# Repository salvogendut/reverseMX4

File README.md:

# reverseMX4: four-slot CPC edge backplane

This project is a four-slot expansion backplane for the Amstrad CPC bus. A short cable connects the computer to a **50-contact male edge tongue on the backplane**. Four vertical, 50-contact female card-edge sockets accept expansion cards that have the classic CPC edge finger pattern. There are no MX4/IDC headers on the backplane.

## Target computers

- CPC 464, 664 and 6128: cable with a 50-contact female edge socket at the computer.
- CPC 464 Plus and 6128 Plus: cable with a 50-contact Delta/Amphenol style plug at the computer.
- The board-end of either cable has a 50-contact female edge socket. The cable must map each **named signal** to the backplane tongue contact in [`docs/cpc-expansion-pinout.csv`](docs/cpc-expansion-pinout.csv); do not rely on the shell orientation or ribbon stripe alone.

The classic CPC expansion port has 25 contacts on each face, 2.54 mm pitch and 1.6 mm nominal card thickness. The Plus uses a 50-contact Delta style connector with the same bus signals. The board does not translate logic or select slots; all four sockets share the expansion bus in parallel. Expansion cards must themselves handle address decoding and bus arbitration. Simultaneous use also depends on the computer's available power and the attached cards' electrical loading.

## Prototype design

- [`reverseMX4.kicad_sch`](reverseMX4.kicad_sch), [`reverseMX4.kicad_pcb`](reverseMX4.kicad_pcb) and [`reverseMX4.kicad_pro`](reverseMX4.kicad_pro) are the editable KiCad 10 project.
- Board outline: 100 × 200 mm including the 65.74 mm wide cable tongue. Four EDAC 50-contact sockets are placed at 35 mm slot pitch.
- Four copper layers: odd-side bus signals on inner layer 1, even-side bus signals on inner layer 2, selected 5 V fill on front, ground fill on back.
- `JP1` selects CPC power (pins 1–2) or external regulated 5 V (pins 2–3). The external input passes through a 3 A hold PTC fuse. The sources are isolated from each other by the removed position of the shunt.
- The 50 tongue pads stop 0.6 mm before the board tip. The EDAC drawing places the contact point approximately 4.06 mm behind the tip, within the 6.9 mm long contact pad. The socket's recommended daughter-board width is 66.04 − 0.30 = 65.74 mm.
- [`docs/assembly.md`](docs/assembly.md) covers cable checks, part placement and manufacturing notes. [`docs/bom.csv`](docs/bom.csv) lists parts. [`docs/preview/schematic.pdf`](docs/preview/schematic.pdf) and [`docs/preview/top-assembly.svg`](docs/preview/top-assembly.svg) are review views.
- [`fab/reverseMX4-A0-gerbers.zip`](fab/reverseMX4-A0-gerbers.zip) contains the four copper layers, masks, silkscreens, outline and separate plated/non-plated drill files. Read [`fab/README.md`](fab/README.md) before ordering.

## 3D rendering

[Open the full-size 3D rendering](docs/preview/board-3d.png). The four socket bodies use a simple local preview model to show position and card openings; their exact housing shape and height have not been verified against a physical EDAC part.

KiCad ERC and DRC pass with zero violations, zero unrouted items and zero schematic parity issues. The PCB is an **untested prototype**: connector mating, card clearance, cable orientation and operation on real CPC/CPC Plus computers still need physical verification before a production run.

The reference URL supplied for this project, `rabs664/Amstrad-CPC-Plus-Expansion-Backplane`, was unavailable during the initial research. Its layout has not been copied. The pin map below comes from Amstrad's CPC 464 manual and Arnold V CPC Plus expansion specification.

## Sources

- [Amstrad CPC 464 user manual, expansion connector page](https://www.manualslib.com/manual/862146/Amstrad-Cpc464.html?page=237)
- [Amstrad Arnold V specification, appendix II](https://www.cpctech.cpcwiki.de/docs/arn5new.html)
- [EDAC 345/395 card-edge connector datasheet](https://www.farnell.com/datasheets/2916867.pdf)
- [CPC expansion power notes](https://www.cpctech.cpcwiki.de/docs/signals.html)
- [EDAC 395 series product specifications](https://edac.net/series/395)

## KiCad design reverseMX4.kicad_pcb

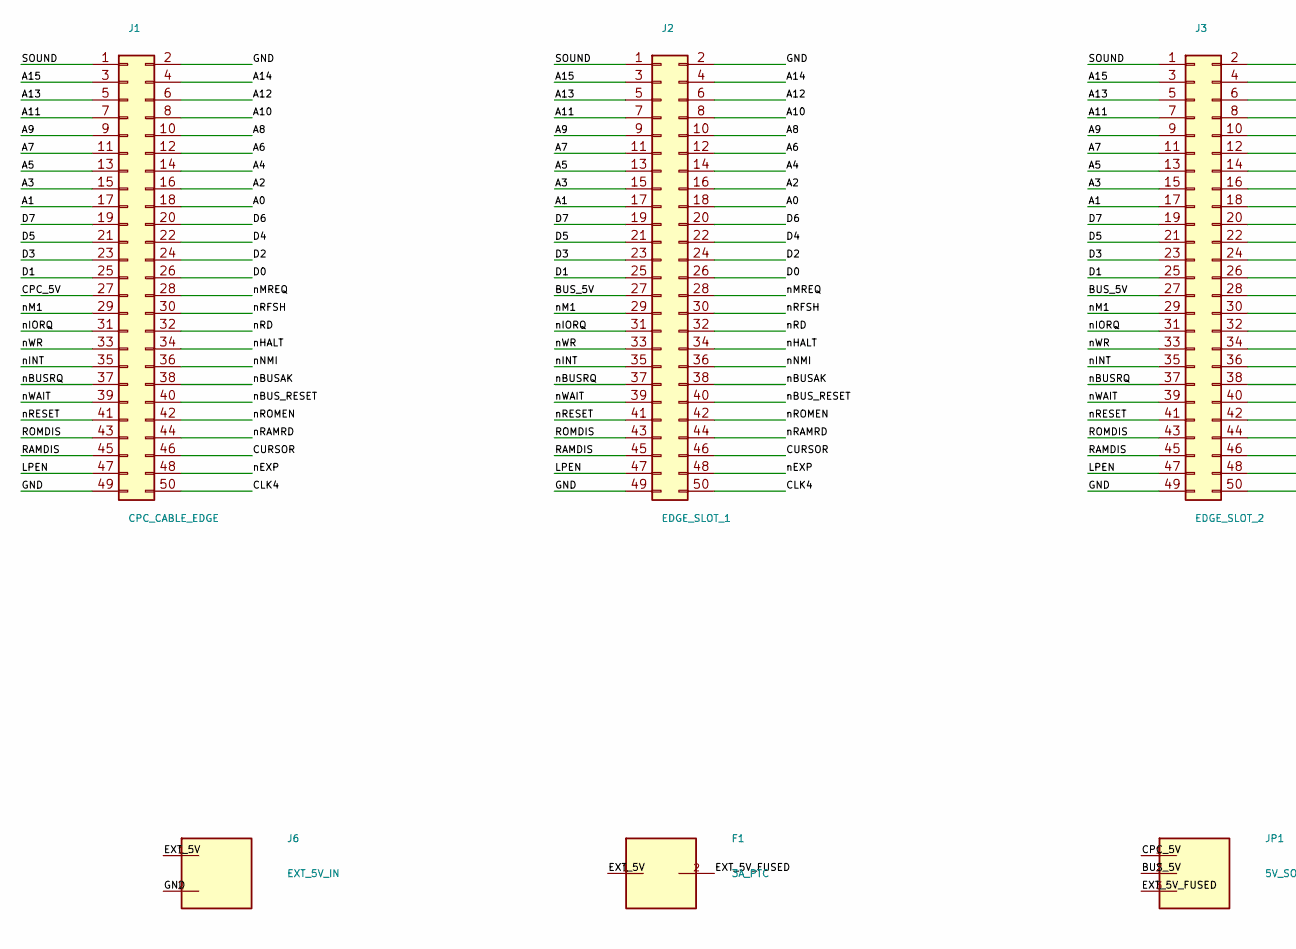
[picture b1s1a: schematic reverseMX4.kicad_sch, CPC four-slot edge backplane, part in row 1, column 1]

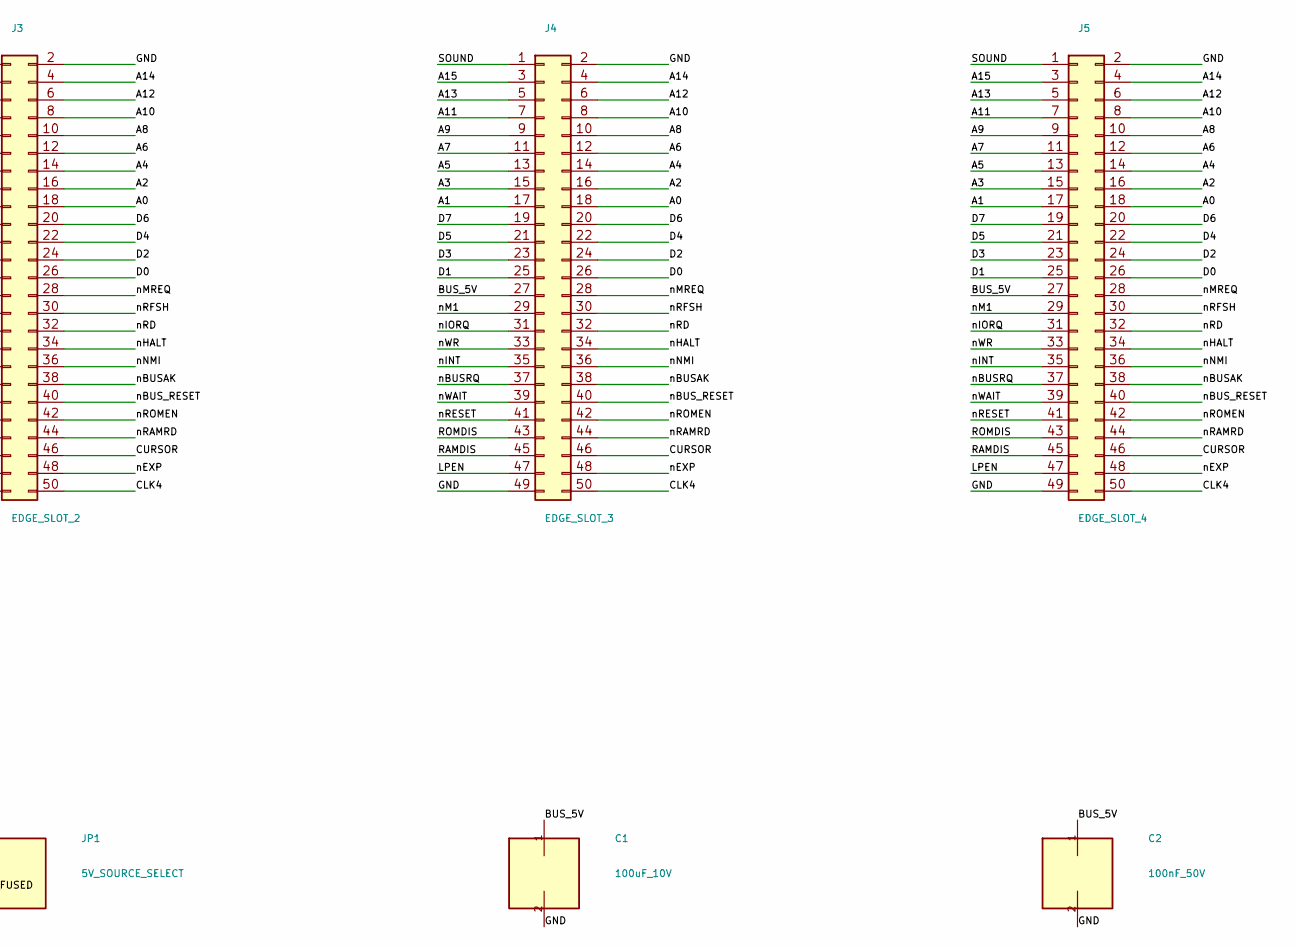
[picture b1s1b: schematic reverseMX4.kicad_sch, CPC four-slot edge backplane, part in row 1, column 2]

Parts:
C1: 100uF_10V; CP_Radial_D6.3mm_P2.50mm
C2: 100nF_50V; C_Disc_D3.0mm_W1.6mm_P2.50mm
F1: 3A_PTC; Fuse_Bourns_MF-RG300
J1: CPC_CABLE_EDGE; CPC_Edge_2x25
J2: EDGE_SLOT_1; EDAC_395-050-521-204
J3: EDGE_SLOT_2; EDAC_395-050-521-204
J4: EDGE_SLOT_3; EDAC_395-050-521-204
J5: EDGE_SLOT_4; EDAC_395-050-521-204
J6: EXT_5V_IN; TerminalBlock_Phoenix_MKDS-1,5-2_1x02_P5.00mm_Horizontal
JP1: 5V_SOURCE_SELECT; PinHeader_1x03_P2.54mm_Vertical

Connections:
/A0: J1.18, J2.18, J3.18, J4.18, J5.18
/A1: J1.17, J2.17, J3.17, J4.17, J5.17
/A2: J1.16, J2.16, J3.16, J4.16, J5.16
/A3: J1.15, J2.15, J3.15, J4.15, J5.15
/A4: J1.14, J2.14, J3.14, J4.14, J5.14
/A5: J1.13, J2.13, J3.13, J4.13, J5.13
/A6: J1.12, J2.12, J3.12, J4.12, J5.12
/A7: J1.11, J2.11, J3.11, J4.11, J5.11
/A8: J1.10, J2.10, J3.10, J4.10, J5.10
/A9: J1.9, J2.9, J3.9, J4.9, J5.9
/A10: J1.8, J2.8, J3.8, J4.8, J5.8
/A11: J1.7, J2.7, J3.7, J4.7, J5.7
/A12: J1.6, J2.6, J3.6, J4.6, J5.6
/A13: J1.5, J2.5, J3.5, J4.5, J5.5
/A14: J1.4, J2.4, J3.4, J4.4, J5.4
/A15: J1.3, J2.3, J3.3, J4.3, J5.3
/BUS_5V: C1.1, C2.1, J2.27, J3.27, J4.27, J5.27, JP1.2
/CLK4: J1.50, J2.50, J3.50, J4.50, J5.50
/CPC_5V: J1.27, JP1.1
/CURSOR: J1.46, J2.46, J3.46, J4.46, J5.46
/D0: J1.26, J2.26, J3.26, J4.26, J5.26
/D1: J1.25, J2.25, J3.25, J4.25, J5.25
/D2: J1.24, J2.24, J3.24, J4.24, J5.24
/D3: J1.23, J2.23, J3.23, J4.23, J5.23
/D4: J1.22, J2.22, J3.22, J4.22, J5.22
/D5: J1.21, J2.21, J3.21, J4.21, J5.21
/D6: J1.20, J2.20, J3.20, J4.20, J5.20
/D7: J1.19, J2.19, J3.19, J4.19, J5.19
/EXT_5V: F1.1, J6.1
/EXT_5V_FUSED: F1.2, JP1.3
/GND: C1.2, C2.2, J1.2, J1.49, J2.2, J2.49, J3.2, J3.49, J4.2, J4.49, J5.2, J5.49, J6.2
/LPEN: J1.47, J2.47, J3.47, J4.47, J5.47
/RAMDIS: J1.45, J2.45, J3.45, J4.45, J5.45
/ROMDIS: J1.43, J2.43, J3.43, J4.43, J5.43
/SOUND: J1.1, J2.1, J3.1, J4.1, J5.1
/nBUSAK: J1.38, J2.38, J3.38, J4.38, J5.38
/nBUSRQ: J1.37, J2.37, J3.37, J4.37, J5.37
/nBUS_RESET: J1.40, J2.40, J3.40, J4.40, J5.40
/nEXP: J1.48, J2.48, J3.48, J4.48, J5.48
/nHALT: J1.34, J2.34, J3.34, J4.34, J5.34
/nINT: J1.35, J2.35, J3.35, J4.35, J5.35
/nIORQ: J1.31, J2.31, J3.31, J4.31, J5.31
/nM1: J1.29, J2.29, J3.29, J4.29, J5.29
/nMREQ: J1.28, J2.28, J3.28, J4.28, J5.28
/nNMI: J1.36, J2.36, J3.36, J4.36, J5.36
/nRAMRD: J1.44, J2.44, J3.44, J4.44, J5.44
/nRD: J1.32, J2.32, J3.32, J4.32, J5.32
/nRESET: J1.41, J2.41, J3.41, J4.41, J5.41
/nRFSH: J1.30, J2.30, J3.30, J4.30, J5.30
/nROMEN: J1.42, J2.42, J3.42, J4.42, J5.42
/nWAIT: J1.39, J2.39, J3.39, J4.39, J5.39
/nWR: J1.33, J2.33, J3.33, J4.33, J5.33

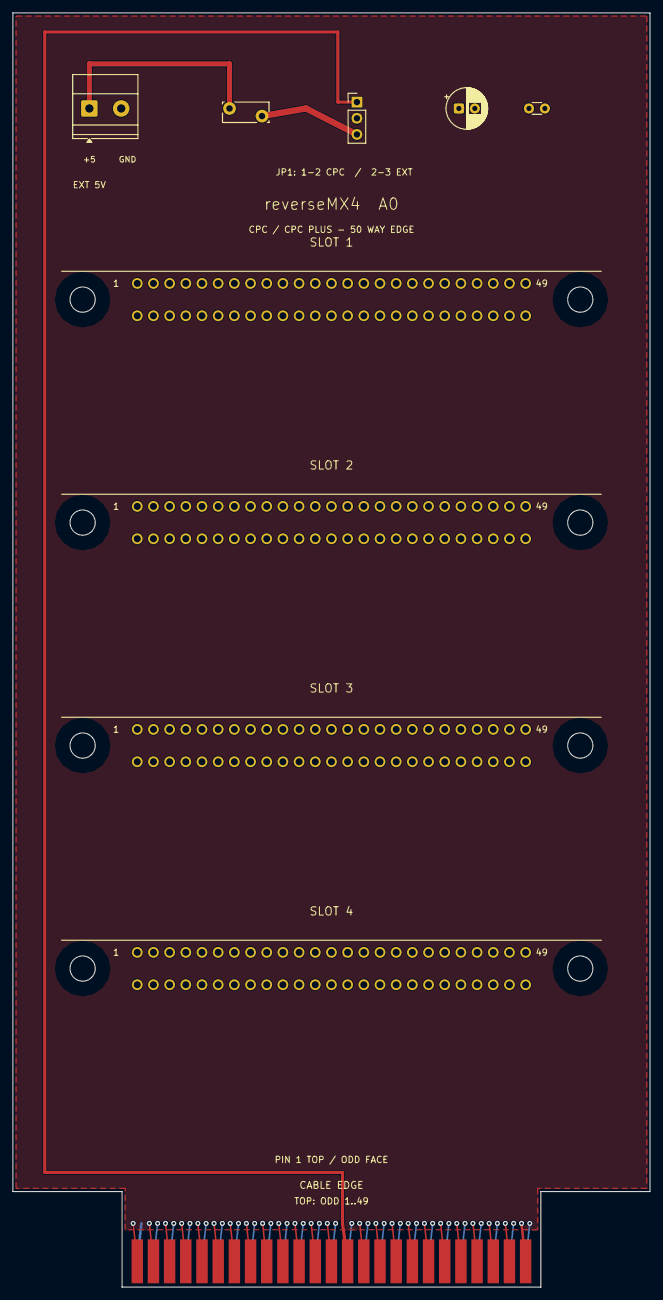
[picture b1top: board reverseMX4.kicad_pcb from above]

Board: 4 copper layers, 100.0 x 200.0 mm, 10 parts (0 on the bottom side), 52 nets.

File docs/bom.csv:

references,quantity,value,manufacturer,manufacturer_part,notes
J1,1,Integrated 50-contact PCB edge tongue,PCB fabrication,,65.74 mm wide; 1.6 mm thick; contacts on both faces
J2 J3 J4 J5,4,50-contact vertical card-edge socket,EDAC,395-050-521-204,2.54 mm pitch; 5.08 mm row spacing; 3.96 mm mounting holes
J6,1,2-position 5.00 mm terminal block,Phoenix Contact,1715022,MKDS 1.5/2; pin 1 +5 V; pin 2 GND
F1,1,3 A hold PTC resettable fuse,Bourns,MF-RG300-0,External 5 V input only
JP1,1,1x3 2.54 mm through-hole header,Samtec,TSW-103-07-G-S,Power source selector
JP1 shunt,1,2-position 2.54 mm shunt,Samtec,SNT-100-BK-G,Place 1-2 for CPC or 2-3 for external power
C1,1,100 uF 10 V radial electrolytic,,,6.3 mm diameter; 2.5 mm lead spacing; pad 1 positive
C2,1,100 nF 50 V ceramic disc,,,3.0 mm body; 2.5 mm lead spacing

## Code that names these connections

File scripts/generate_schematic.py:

#!/usr/bin/env python3
"""Generate the source schematic from the reviewed CPC contact table."""

import csv
import pathlib
import re
import uuid

ROOT = pathlib.Path(__file__).resolve().parents[1]
NAME = "reverseMX4"
SHEET_UUID = str(uuid.uuid5(uuid.NAMESPACE_URL, "reverseMX4/schematic/root"))


def uid(key):
    return str(uuid.uuid5(uuid.NAMESPACE_URL, f"reverseMX4/{key}"))


def quoted(s):
    return '"' + s.replace('\\', '\\\\').replace('"', '\\"') + '"'


def extract_symbol(source, name):
    text = source.read_text()
    match = re.search(r'\(symbol "' + re.escape(name) + r'"', text)
    if not match:
        raise ValueError(f"Cannot find {name} in {source}")
    start = match.start()
    depth = 0
    in_string = False
    escaped = False
    for i in range(start, len(text)):
        ch = text[i]
        if in_string:
            if escaped:
                escaped = False
            elif ch == '\\':
                escaped = True
            elif ch == '"':
                in_string = False
        elif ch == '"':
            in_string = True
        elif ch == '(':
            depth += 1
        elif ch == ')':
            depth -= 1
            if depth == 0:
                return text[start:i + 1]
    raise ValueError(f"Unbalanced symbol {name}")


SYMBOLS = pathlib.Path('/var/lib/flatpak/runtime/org.kicad.kicad.Library/x86_64/stable/active/files/symbols')
connector = extract_symbol(SYMBOLS / 'Connector_Generic.kicad_sym', 'Conn_02x25_Odd_Even')
connector = connector.replace('(symbol "Conn_02x25_Odd_Even"', '(symbol "Connector_Generic:Conn_02x25_Odd_Even"', 1)
pinout = list(csv.DictReader((ROOT / 'docs/cpc-expansion-pinout.csv').open()))
assert len(pinout) == 50

body = []


def label(name, x, y, tag):
    body.append(f'(label {quoted(name)} (at {x:.3f} {y:.3f} 0) (effects (font (size 1 1)) (justify left bottom)) (uuid "{uid(tag)}"))')


def wire(x1, y1, x2, y2, tag):
    body.append(f'(wire (pts (xy {x1:.3f} {y1:.3f}) (xy {x2:.3f} {y2:.3f})) (stroke (width 0) (type default)) (uuid "{uid(tag)}"))')


def property_(key, val, x, y, hide=False):
    return f'(property {quoted(key)} {quoted(val)} (at {x:.3f} {y:.3f} 0) {"(hide yes)" if hide else ""} (effects (font (size 1 1)) (justify left)))'


for index, x in enumerate((38.1, 114.3, 190.5, 266.7, 342.9), start=1):
    y = 120.65
    ref = f'J{index}'
    value = 'CPC_CABLE_EDGE' if index == 1 else f'EDGE_SLOT_{index - 1}'
    fp = 'reverseMX4:CPC_Edge_2x25' if index == 1 else 'reverseMX4:EDAC_395-050-521-204'
    pins = ''.join(f'(pin "{n}" (uuid "{uid(ref + "/pin/" + str(n))}"))' for n in range(1, 51))
    body.append(f'''(symbol (lib_id "Connector_Generic:Conn_02x25_Odd_Even") (at {x} {y} 0) (unit 1) (in_bom yes) (on_board yes) (dnp no) (uuid "{uid(ref)}")
      {property_("Reference", ref, x, 85)}
      {property_("Value", value, x, 155)}
      {property_("Footprint", fp, x, y, True)}
      {property_("Datasheet", "", x, y, True)}
      {pins}
      (instances (project "{NAME}" (path "/{SHEET_UUID}" (reference "{ref}") (unit 1)))))''')
    for row in pinout:
        n = int(row['contact'])
        sig = row['signal']
        if sig == 'GND':
            sig = 'GND'
        elif sig == '+5V':
            sig = 'CPC_5V' if index == 1 else 'BUS_5V'
        elif sig.startswith('/'):
            sig = 'n' + sig[1:]
        # Schematic symbol pin 1 is at (-5.08,+30.48) in symbol coordinates.
        yy = y - 30.48 + ((n - 1) // 2) * 2.54
        if n % 2:
            xpin, xend = x - 5.08, x - 15.24
        else:
            xpin, xend = x + 7.62, x + 17.78
        wire(xpin, yy, xend, yy, f'{ref}/wire/{n}')
        label(sig, xend, yy, f'{ref}/label/{n}')


def simple_symbol(name, pins, width=10, height=10):
    shape = f'(rectangle (start {-width/2} {height/2}) (end {width/2} {-height/2}) (stroke (width 0.254) (type default)) (fill (type background)))'
    ptxt = ''
    for num, px, py, angle in pins:
        ptxt += f'(pin passive line (at {px} {py} {angle}) (length 5.08) (name "Pin_{num}" (effects (font (size 1 1)))) (number "{num}" (effects (font (size 1 1)))))'
    return f'''(symbol "reverseMX4:{name}" (pin_names (offset 0.5) (hide yes)) (in_bom yes) (on_board yes)
      (property "Reference" "X" (at 0 {height/2+2.54} 0) (effects (font (size 1 1))))
      (property "Value" "{name}" (at 0 {-height/2-2.54} 0) (effects (font (size 1 1))))
      (symbol "{name}_0_1" {shape})
      (symbol "{name}_1_1" {ptxt}))'''


parts = [
    ('J6', 'EXT_5V_IN', 'reverseMX4:PowerIn_2', 'TerminalBlock_Phoenix:TerminalBlock_Phoenix_MKDS-1,5-2_1x02_P5.00mm_Horizontal', 50.8, 205.74, [(1, 'EXT_5V', 43.18, 203.2), (2, 'GND', 43.18, 208.28)]),
    ('F1', '3A_PTC', 'reverseMX4:Series_2', 'Fuse:Fuse_Bourns_MF-RG300', 114.3, 205.74, [(1, 'EXT_5V', 106.68, 205.74), (2, 'EXT_5V_FUSED', 121.92, 205.74)]),
    ('JP1', '5V_SOURCE_SELECT', 'reverseMX4:Select_3', 'Connector_PinHeader_2.54mm:PinHeader_1x03_P2.54mm_Vertical', 190.5, 205.74, [(1, 'CPC_5V', 182.88, 203.2), (2, 'BUS_5V', 182.88, 205.74), (3, 'EXT_5V_FUSED', 182.88, 208.28)]),
    ('C1', '100uF_10V', 'reverseMX4:Shunt_2', 'Capacitor_THT:CP_Radial_D6.3mm_P2.50mm', 266.7, 205.74, [(1, 'BUS_5V', 266.7, 198.12), (2, 'GND', 266.7, 213.36)]),
    ('C2', '100nF_50V', 'reverseMX4:Shunt_2', 'Capacitor_THT:C_Disc_D3.0mm_W1.6mm_P2.50mm', 342.9, 205.74, [(1, 'BUS_5V', 342.9, 198.12), (2, 'GND', 342.9, 213.36)]),
]
power_symbols = [
    simple_symbol('PowerIn_2', [(1, -7.62, 2.54, 0), (2, -7.62, -2.54, 0)]),
    simple_symbol('Series_2', [(1, -7.62, 0, 0), (2, 7.62, 0, 180)]),
    simple_symbol('Select_3', [(1, -7.62, 2.54, 0), (2, -7.62, 0, 0), (3, -7.62, -2.54, 0)]),
    simple_symbol('Shunt_2', [(1, 0, 7.62, 270), (2, 0, -7.62, 90)]),
]
(ROOT / 'reverseMX4.kicad_sym').write_text(
    '(kicad_symbol_lib (version 20231120) (generator "kicad_symbol_editor")\n'
    + '\n'.join(s.replace('(symbol "reverseMX4:', '(symbol "', 1) for s in power_symbols)
    + '\n)\n'
)
(ROOT / 'sym-lib-table').write_text('(sym_lib_table (lib (name "reverseMX4") (type "KiCad") (uri "${KIPRJMOD}/reverseMX4.kicad_sym") (options "") (descr "CPC backplane local symbols")))\n')
for ref, value, lib, fp, x, y, pins in parts:
    plist = ''.join(f'(pin "{p}" (uuid "{uid(ref + "/pin/" + str(p))}"))' for p, *_ in pins)
    body.append(f'''(symbol (lib_id "{lib}") (at {x} {y} 0) (unit 1) (in_bom yes) (on_board yes) (dnp no) (uuid "{uid(ref)}")
    {property_("Reference", ref, x + 10, y - 5)}
    {property_("Value", value, x + 10, y)}
    {property_("Footprint", fp, x, y, True)}
    {property_("Datasheet", "", x, y, True)}
    {plist}
    (instances (project "{NAME}" (path "/{SHEET_UUID}" (reference "{ref}") (unit 1)))))''')
    for p, net, px, py in pins:
        label(net, px, py, f'{ref}/label/{p}')

output = f'''(kicad_sch (version 20250114) (generator "eeschema") (uuid "{SHEET_UUID}") (paper "A3")
(title_block (title "CPC four-slot edge backplane") (date "2026-10-09") (rev "A0") (comment 1 "CPC / CPC Plus via model-specific cable") (comment 2 "External 5V must be regulated; select one power source"))
(lib_symbols {connector} {' '.join(power_symbols)})
{' '.join(body)}
(embedded_fonts no))
'''
(ROOT / f'{NAME}.kicad_sch').write_text(output)
print(f'Wrote {NAME}.kicad_sch')
